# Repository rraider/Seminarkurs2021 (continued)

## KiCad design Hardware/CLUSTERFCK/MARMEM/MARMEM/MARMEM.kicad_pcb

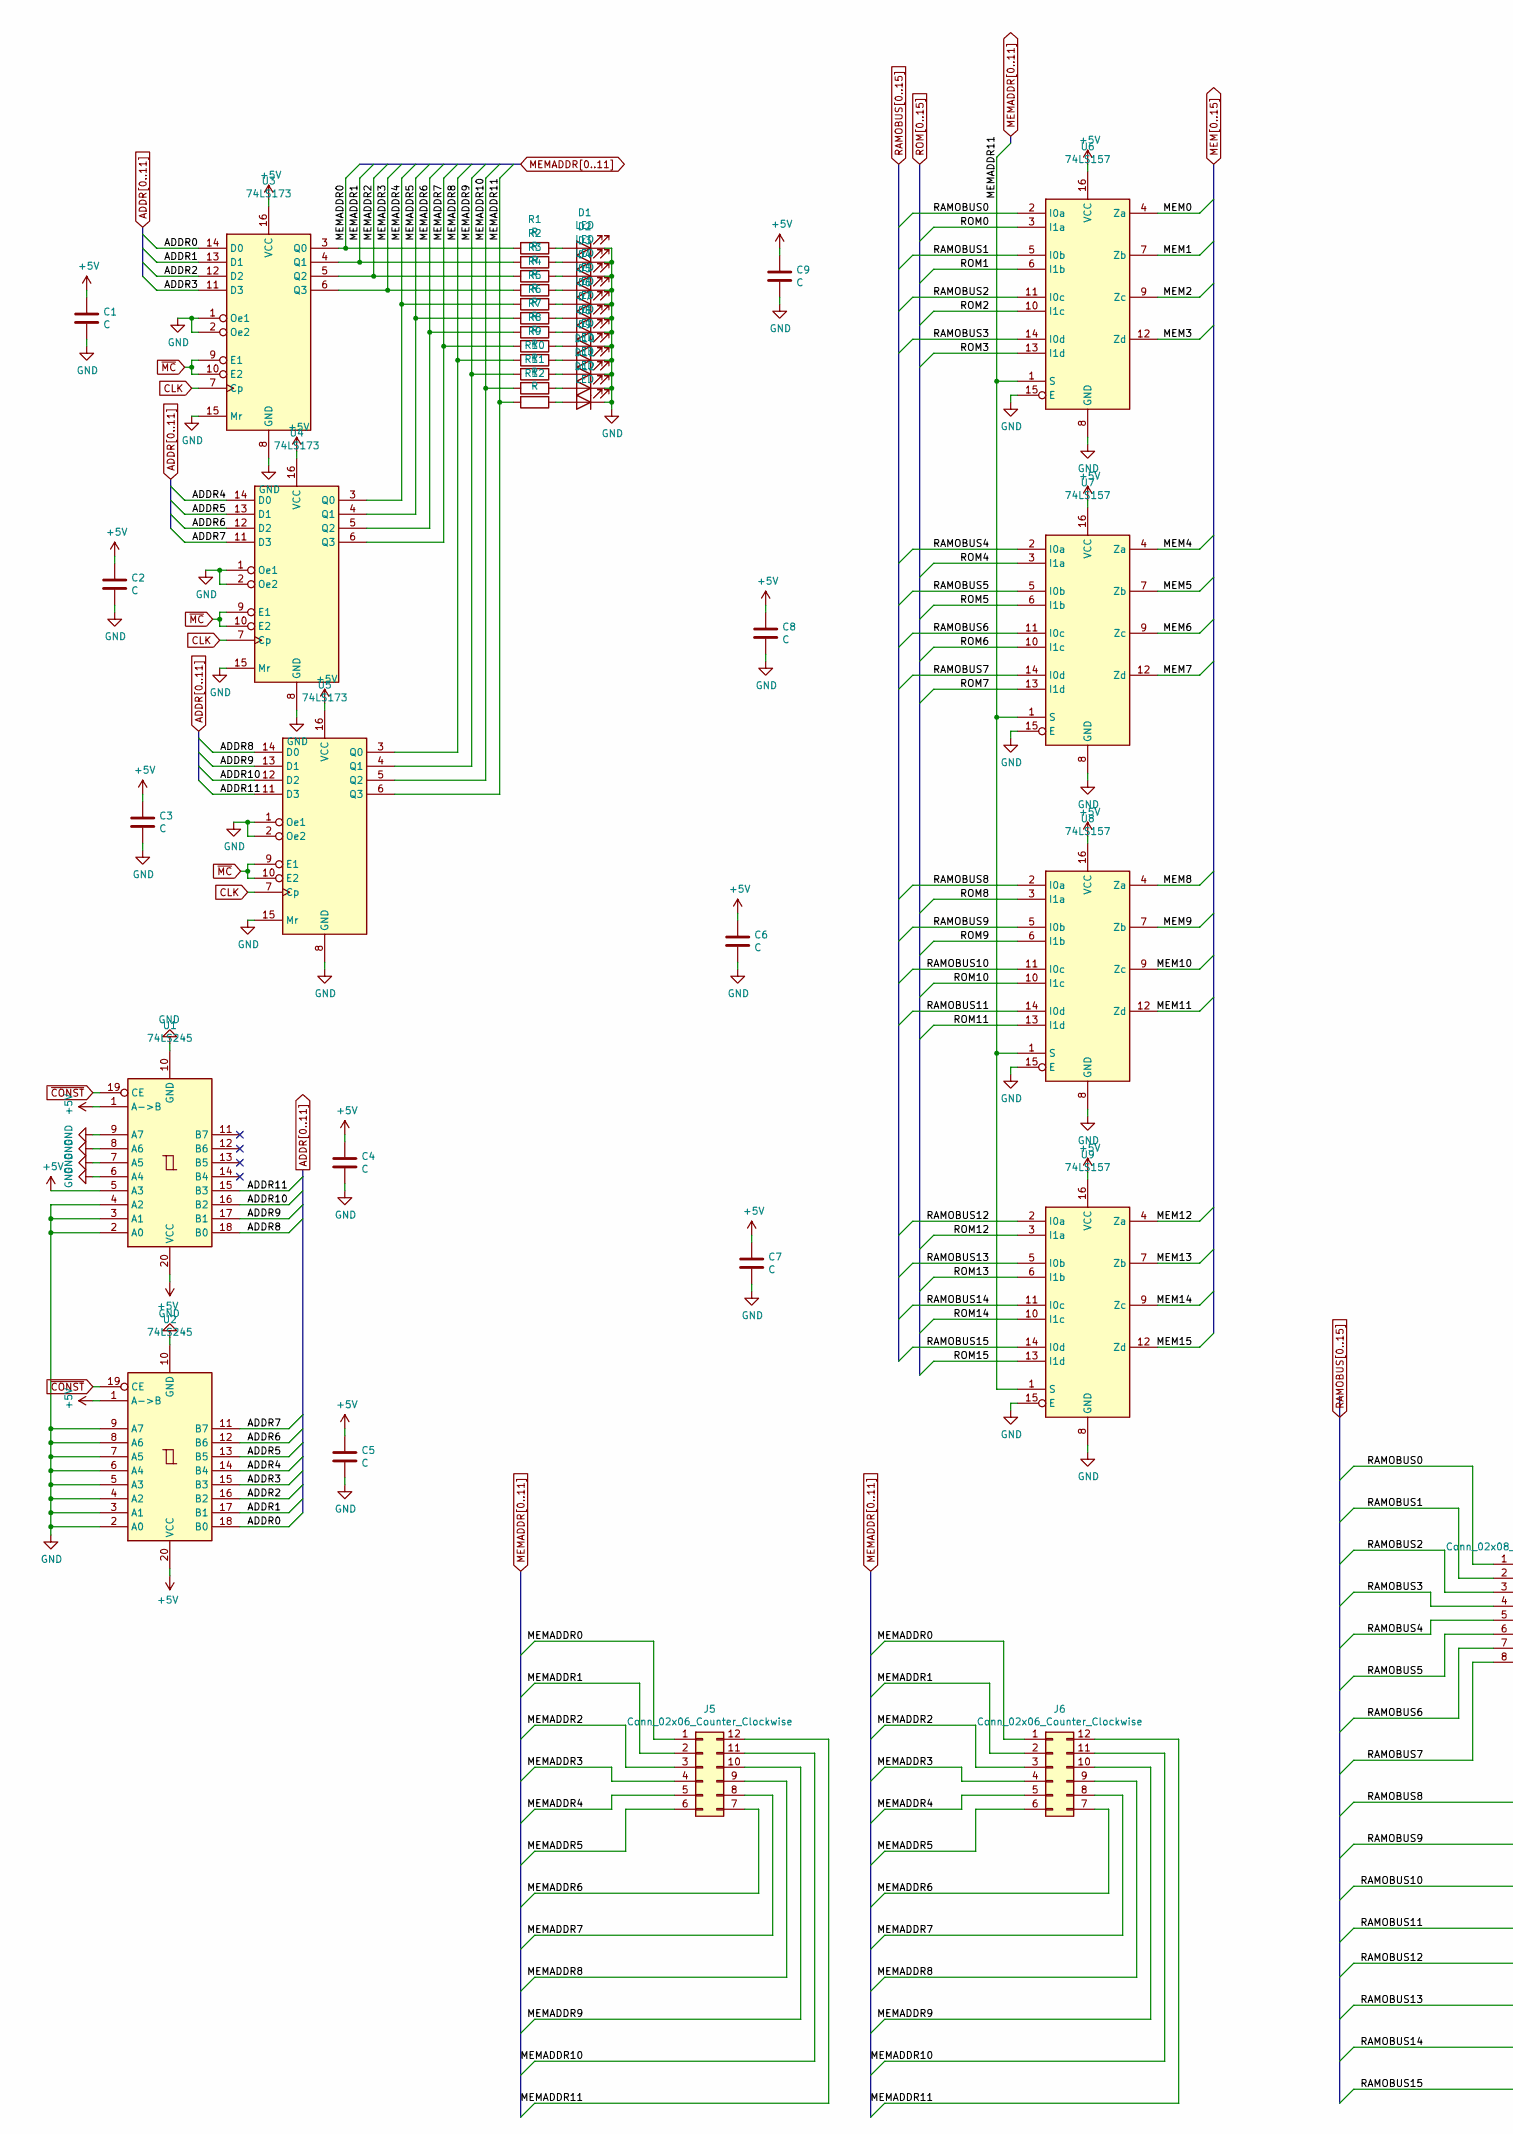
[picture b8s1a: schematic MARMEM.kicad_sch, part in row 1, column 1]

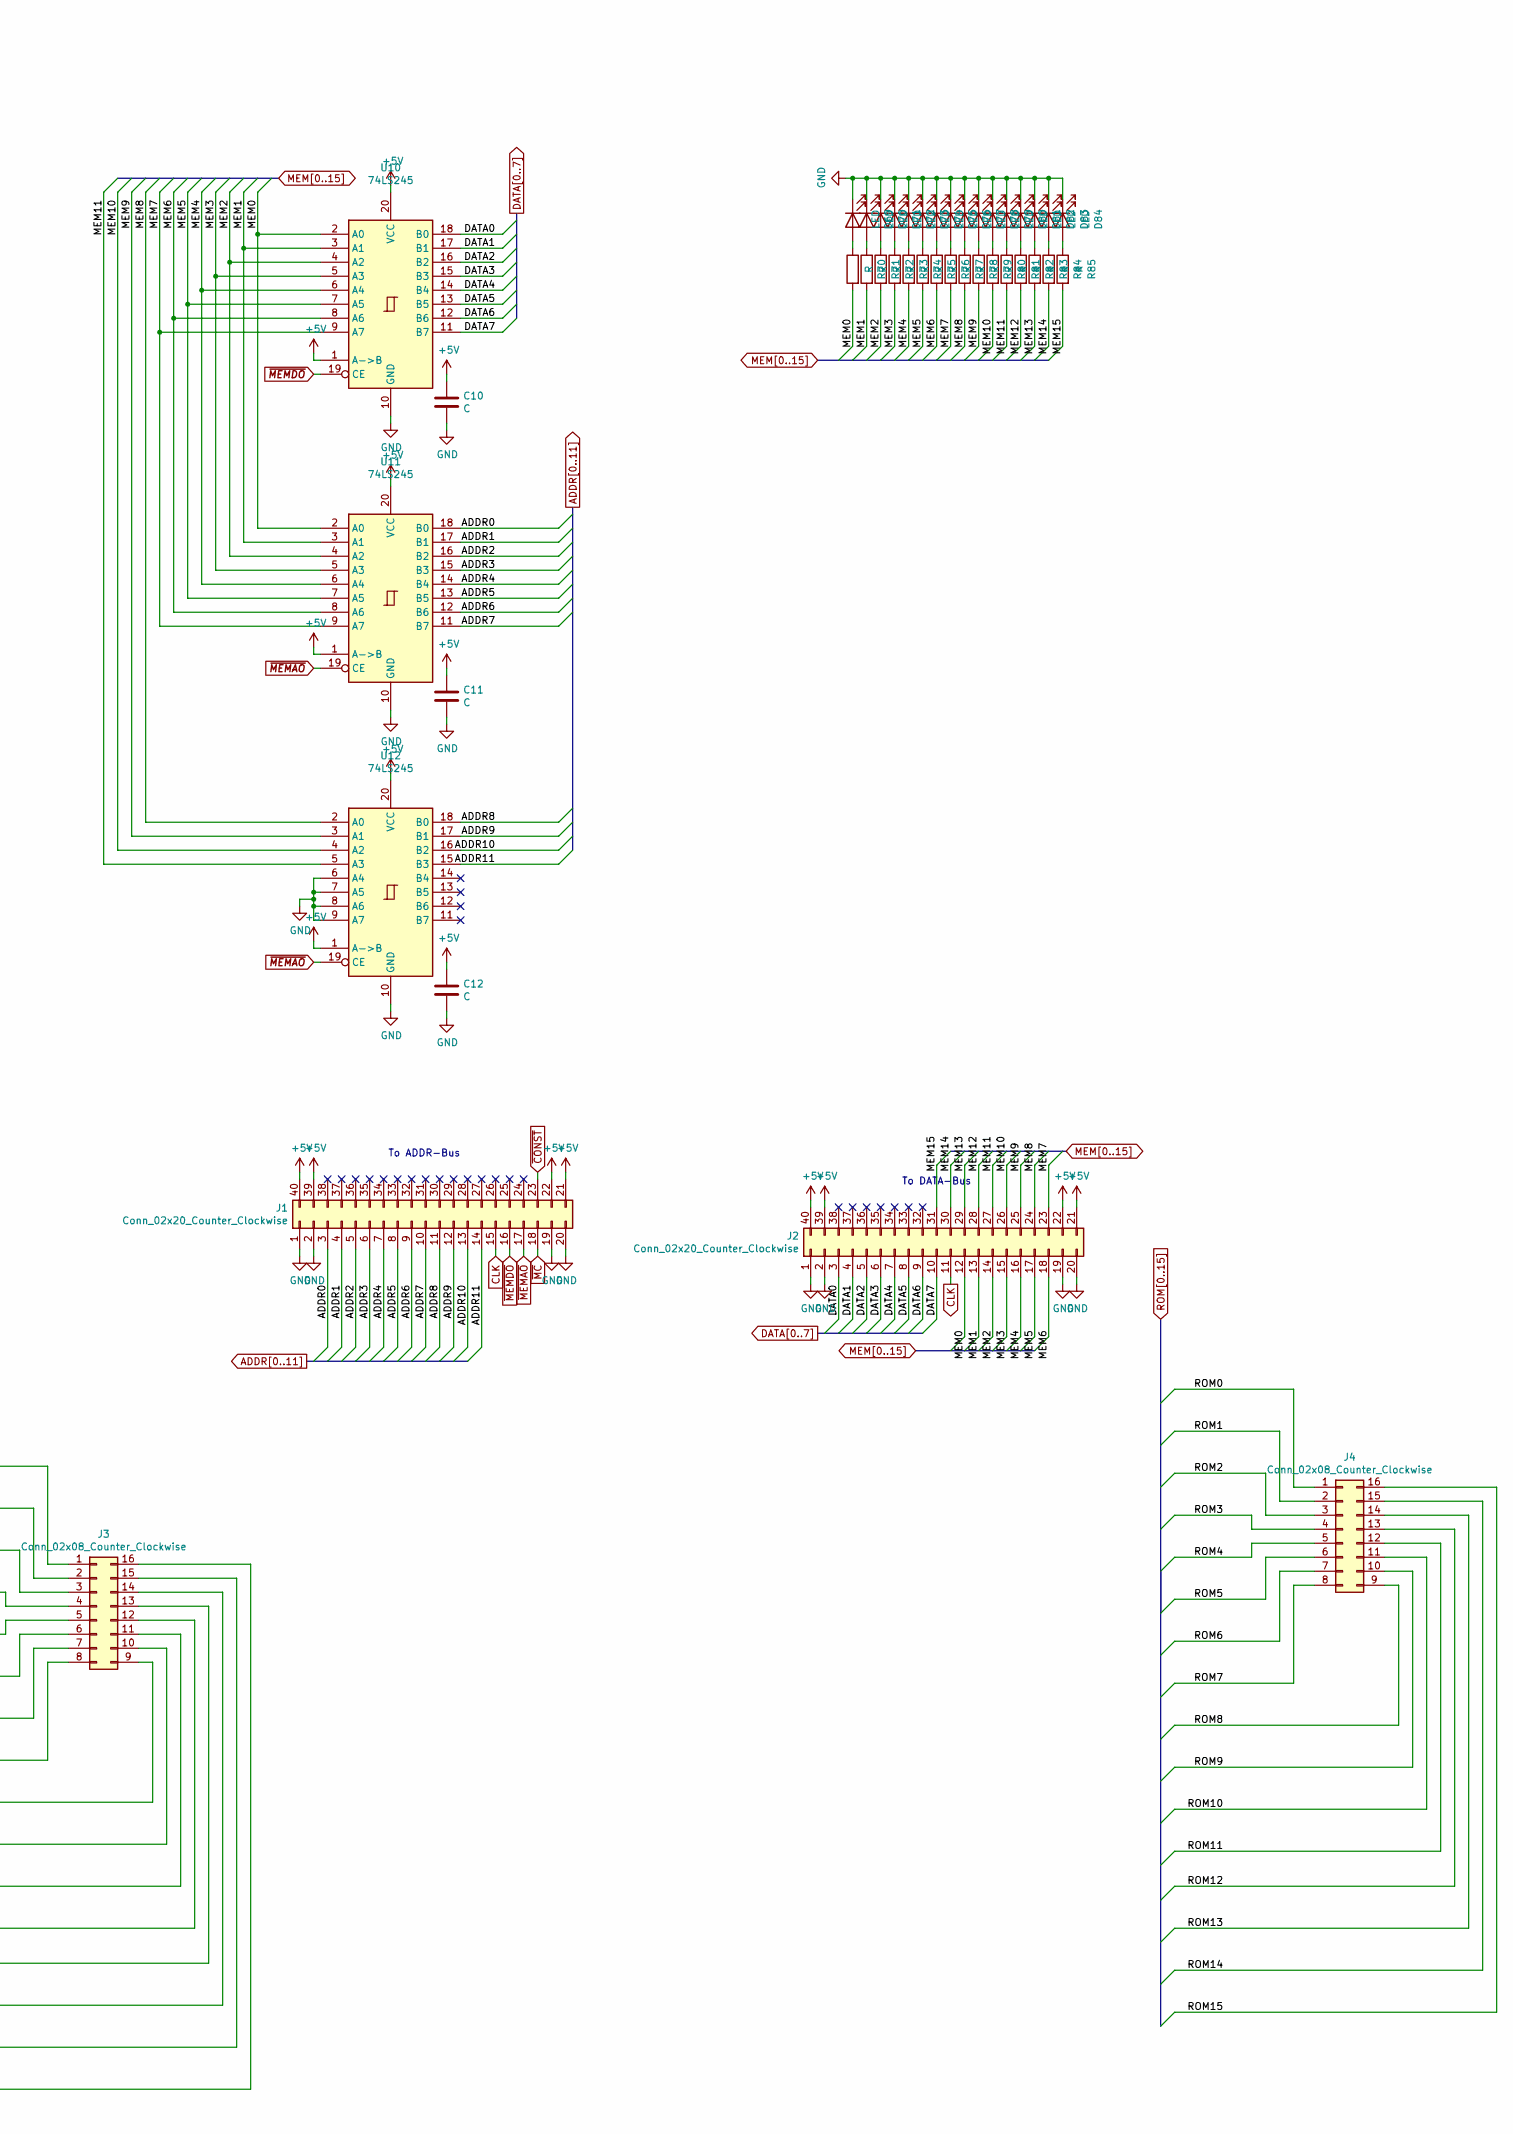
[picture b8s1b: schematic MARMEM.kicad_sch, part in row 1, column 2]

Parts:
C1, C2, C3, C4, C5, C6, C7, C8, C9, C10, C11, C12: C; C_0805_2012Metric_Pad1.15x1.40mm_HandSolder
D1, D2, D3, D4, D5, D6, D7, D8, D9, D10, D11, D12, D69, D70, D71, D72, D73, D74, D75, D76, D77, D78, D79, D80, D81, D82, D83, D84: LED; LED_D5.0mm
J1, J2: Conn_02x20_Counter_Clockwise; PinSocket_2x20_P2.54mm_Horizontal
J3, J4: Conn_02x08_Counter_Clockwise; PinHeader_2x08_P2.54mm_Horizontal
J5, J6: Conn_02x06_Counter_Clockwise; PinHeader_2x06_P2.54mm_Horizontal
R1, R2, R3, R4, R5, R6, R7, R8, R9, R10, R11, R12, R70, R71, R72, R73, R74, R75, R76, R77, R78, R79, R80, R81, R82, R83, R84, R85: R; R_0805_2012Metric_Pad1.15x1.40mm_HandSolder
U1, U2, U10, U11, U12: 74LS245; SOIC-20W_7.5x12.8mm_P1.27mm
U3, U4, U5: 74LS173; SOP-16_3.9x9.9mm_P1.27mm
U6, U7, U8, U9: 74LS157; SOP-16_3.9x9.9mm_P1.27mm

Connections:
+5V: C1.1, C2.1, C3.1, C4.1, C5.1, C6.1, C7.1, C8.1, C9.1, C10.1, C11.1, C12.1, J1.21, J1.22, J1.39, J1.40, J2.21, J2.22, J2.39, J2.40, U1.1 (A->B), U1.5 (A3), U1.20 (VCC), U2.1 (A->B), U2.20 (VCC), U3.16 (VCC), U4.16 (VCC), U5.16 (VCC), U6.16 (VCC), U7.16 (VCC), U8.16 (VCC), U9.16 (VCC), U10.1 (A->B), U10.20 (VCC), U11.1 (A->B), U11.20 (VCC), U12.1 (A->B), U12.20 (VCC)
ADDR0: J1.3, U2.18 (B0), U3.14 (D0), U11.18 (B0)
ADDR1: J1.4, U2.17 (B1), U3.13 (D1), U11.17 (B1)
ADDR2: J1.5, U2.16 (B2), U3.12 (D2), U11.16 (B2)
ADDR3: J1.6, U2.15 (B3), U3.11 (D3), U11.15 (B3)
ADDR4: J1.7, U2.14 (B4), U4.14 (D0), U11.14 (B4)
ADDR5: J1.8, U2.13 (B5), U4.13 (D1), U11.13 (B5)
ADDR6: J1.9, U2.12 (B6), U4.12 (D2), U11.12 (B6)
ADDR7: J1.10, U2.11 (B7), U4.11 (D3), U11.11 (B7)
ADDR8: J1.11, U1.18 (B0), U5.14 (D0), U12.18 (B0)
ADDR9: J1.12, U1.17 (B1), U5.13 (D1), U12.17 (B1)
ADDR10: J1.13, U1.16 (B2), U5.12 (D2), U12.16 (B2)
ADDR11: J1.14, U1.15 (B3), U5.11 (D3), U12.15 (B3)
CLK: J1.15, J2.11, U3.7 (Cp), U4.7 (Cp), U5.7 (Cp)
DATA0: J2.3, U10.18 (B0)
DATA1: J2.4, U10.17 (B1)
DATA2: J2.5, U10.16 (B2)
DATA3: J2.6, U10.15 (B3)
DATA4: J2.7, U10.14 (B4)
DATA5: J2.8, U10.13 (B5)
DATA6: J2.9, U10.12 (B6)
DATA7: J2.10, U10.11 (B7)
GND: C1.2, C2.2, C3.2, C4.2, C5.2, C6.2, C7.2, C8.2, C9.2, C10.2, C11.2, C12.2, D1.1 (K), D2.1 (K), D3.1 (K), D4.1 (K), D5.1 (K), D6.1 (K), D7.1 (K), D8.1 (K), D9.1 (K), D10.1 (K), D11.1 (K), D12.1 (K), D69.1 (K), D70.1 (K), D71.1 (K), D72.1 (K), D73.1 (K), D74.1 (K), D75.1 (K), D76.1 (K), D77.1 (K), D78.1 (K), D79.1 (K), D80.1 (K), D81.1 (K), D82.1 (K), D83.1 (K), D84.1 (K), J1.1, J1.2, J1.19, J1.20, J2.1, J2.2, J2.19, J2.20, U1.2 (A0), U1.3 (A1), U1.4 (A2), U1.6 (A4), U1.7 (A5), U1.8 (A6), U1.9 (A7), U1.10 (GND), U2.2 (A0), U2.3 (A1), U2.4 (A2), U2.5 (A3), U2.6 (A4), U2.7 (A5), U2.8 (A6), U2.9 (A7), U2.10 (GND), U3.1 (Oe1), U3.2 (Oe2), U3.8 (GND), U3.15 (Mr), U4.1 (Oe1), U4.2 (Oe2), U4.8 (GND), U4.15 (Mr), U5.1 (Oe1), U5.2 (Oe2), U5.8 (GND), U5.15 (Mr), U6.8 (GND), U6.15 (E), U7.8 (GND), U7.15 (E), U8.8 (GND), U8.15 (E), U9.8 (GND), U9.15 (E), U10.10 (GND), U11.10 (GND), U12.6 (A4), U12.7 (A5), U12.8 (A6), U12.9 (A7), U12.10 (GND)
MEM0: J2.12, R70.2, U6.4 (Za), U10.2 (A0), U11.2 (A0)
MEM1: J2.13, R71.2, U6.7 (Zb), U10.3 (A1), U11.3 (A1)
MEM2: J2.14, R72.2, U6.9 (Zc), U10.4 (A2), U11.4 (A2)
MEM3: J2.15, R73.2, U6.12 (Zd), U10.5 (A3), U11.5 (A3)
MEM4: J2.16, R74.2, U7.4 (Za), U10.6 (A4), U11.6 (A4)
MEM5: J2.17, R75.2, U7.7 (Zb), U10.7 (A5), U11.7 (A5)
MEM6: J2.18, R76.2, U7.9 (Zc), U10.8 (A6), U11.8 (A6)
MEM7: J2.23, R77.2, U7.12 (Zd), U10.9 (A7), U11.9 (A7)
MEM8: J2.24, R78.2, U8.4 (Za), U12.2 (A0)
MEM9: J2.25, R79.2, U8.7 (Zb), U12.3 (A1)
MEM10: J2.26, R80.2, U8.9 (Zc), U12.4 (A2)
MEM11: J2.27, R81.2, U8.12 (Zd), U12.5 (A3)
MEM12: J2.28, R82.2, U9.4 (Za)
MEM13: J2.29, R83.2, U9.7 (Zb)
MEM14: J2.30, R84.2, U9.9 (Zc)
MEM15: J2.31, R85.2, U9.12 (Zd)
MEMADDR0: J5.1, J6.1, R1.2, U3.3 (Q0)
MEMADDR1: J5.2, J6.2, R2.2, U3.4 (Q1)
MEMADDR2: J5.3, J6.3, R3.2, U3.5 (Q2)
MEMADDR3: J5.4, J6.4, R4.2, U3.6 (Q3)
MEMADDR4: J5.5, J6.5, R5.2, U4.3 (Q0)
MEMADDR5: J5.6, J6.6, R6.2, U4.4 (Q1)
MEMADDR6: J5.7, J6.7, R7.2, U4.5 (Q2)
MEMADDR7: J5.8, J6.8, R8.2, U4.6 (Q3)
MEMADDR8: J5.9, J6.9, R9.2, U5.3 (Q0)
MEMADDR9: J5.10, J6.10, R10.2, U5.4 (Q1)
MEMADDR10: J5.11, J6.11, R11.2, U5.5 (Q2)
MEMADDR11: J5.12, J6.12, R12.2, U5.6 (Q3), U6.1 (S), U7.1 (S), U8.1 (S), U9.1 (S)
unnamed: D1.2 (A), R1.1
unnamed: D2.2 (A), R2.1
unnamed: D3.2 (A), R3.1
unnamed: D4.2 (A), R4.1
unnamed: D5.2 (A), R5.1
unnamed: D6.2 (A), R6.1
unnamed: D7.2 (A), R7.1
unnamed: D8.2 (A), R8.1
unnamed: D9.2 (A), R9.1
unnamed: D10.2 (A), R10.1
unnamed: D11.2 (A), R11.1
unnamed: D12.2 (A), R12.1
unnamed: D69.2 (A), R70.1
unnamed: D70.2 (A), R71.1
unnamed: D71.2 (A), R72.1
unnamed: D72.2 (A), R73.1
unnamed: D73.2 (A), R74.1
unnamed: D74.2 (A), R75.1
unnamed: D75.2 (A), R76.1
unnamed: D76.2 (A), R77.1
unnamed: D77.2 (A), R78.1
unnamed: D78.2 (A), R79.1
unnamed: D79.2 (A), R80.1
unnamed: D80.2 (A), R81.1
unnamed: D81.2 (A), R82.1
unnamed: D82.2 (A), R83.1
unnamed: D83.2 (A), R84.1
unnamed: D84.2 (A), R85.1
RAMOBUS0: J3.1, U6.2 (I0a)
RAMOBUS1: J3.2, U6.5 (I0b)
RAMOBUS2: J3.3, U6.11 (I0c)
RAMOBUS3: J3.4, U6.14 (I0d)
RAMOBUS4: J3.5, U7.2 (I0a)
RAMOBUS5: J3.6, U7.5 (I0b)
RAMOBUS6: J3.7, U7.11 (I0c)
RAMOBUS7: J3.8, U7.14 (I0d)
RAMOBUS8: J3.9, U8.2 (I0a)
RAMOBUS9: J3.10, U8.5 (I0b)
RAMOBUS10: J3.11, U8.11 (I0c)
RAMOBUS11: J3.12, U8.14 (I0d)
RAMOBUS12: J3.13, U9.2 (I0a)
RAMOBUS13: J3.14, U9.5 (I0b)
RAMOBUS14: J3.15, U9.11 (I0c)
RAMOBUS15: J3.16, U9.14 (I0d)
ROM0: J4.1, U6.3 (I1a)
ROM1: J4.2, U6.6 (I1b)
ROM2: J4.3, U6.10 (I1c)
ROM3: J4.4, U6.13 (I1d)
ROM4: J4.5, U7.3 (I1a)
ROM5: J4.6, U7.6 (I1b)
ROM6: J4.7, U7.10 (I1c)
ROM7: J4.8, U7.13 (I1d)
ROM8: J4.9, U8.3 (I1a)
ROM9: J4.10, U8.6 (I1b)
ROM10: J4.11, U8.10 (I1c)
ROM11: J4.12, U8.13 (I1d)
ROM12: J4.13, U9.3 (I1a)
ROM13: J4.14, U9.6 (I1b)
ROM14: J4.15, U9.10 (I1c)
ROM15: J4.16, U9.13 (I1d)
~CONST: J1.23, U1.19 (CE), U2.19 (CE)
~MC: J1.18, U3.9 (E1), U3.10 (E2), U4.9 (E1), U4.10 (E2), U5.9 (E1), U5.10 (E2)
~MEMAO: J1.17, U11.19 (CE), U12.19 (CE)
~MEMDO: J1.16, U10.19 (CE)

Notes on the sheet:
To ADDR-Bus
To DATA-Bus

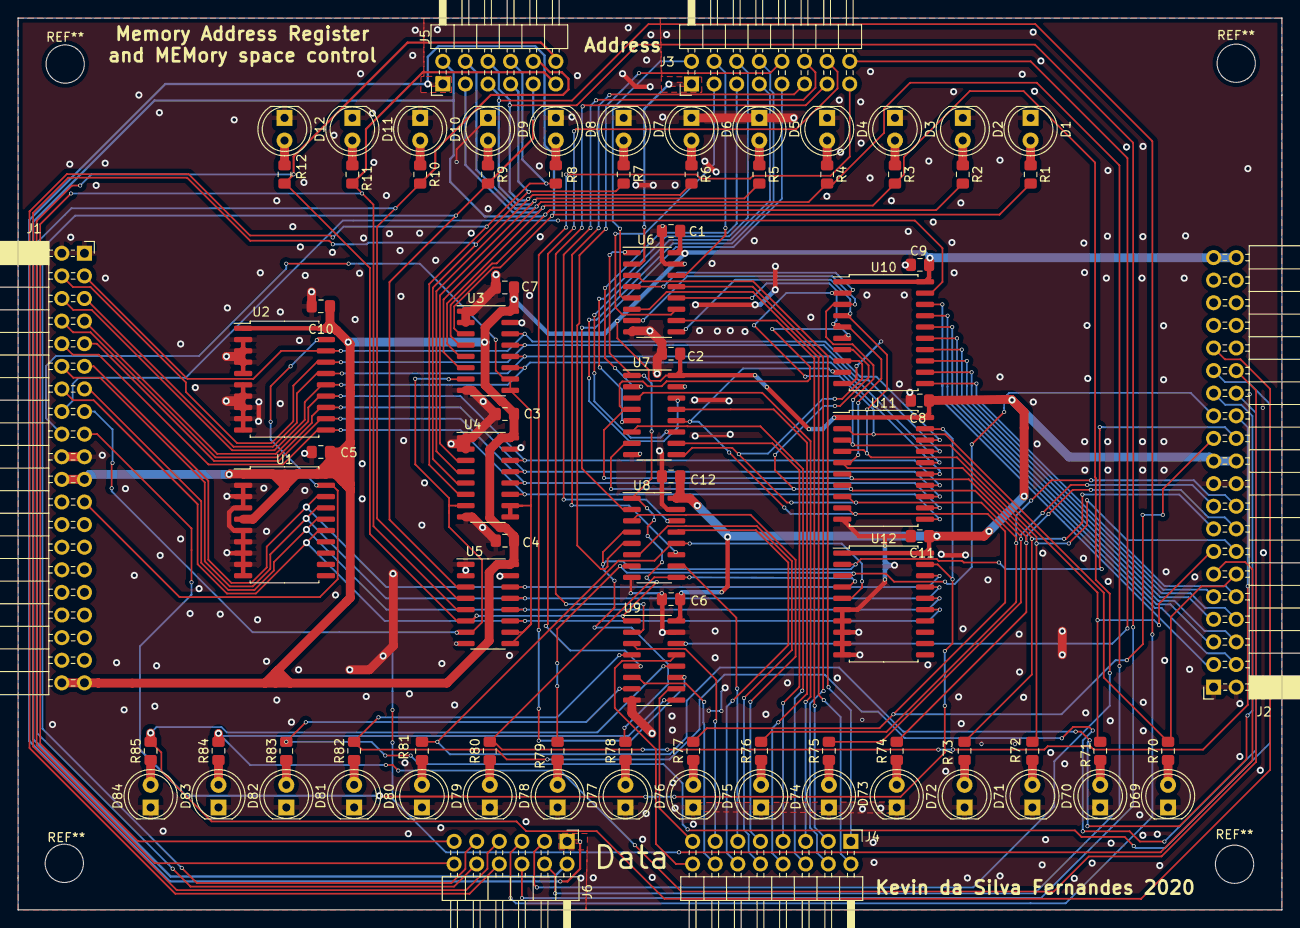
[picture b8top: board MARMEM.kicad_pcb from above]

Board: 2 copper layers, 142.0 x 100.2 mm, 86 parts (0 on the bottom side), 115 nets.

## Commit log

2020-05-05 added lib folder
2020-05-06 finished ALU
2020-05-06 added main file
2020-05-06 added regsiter A and B
2020-05-06 wir essen jetzt
2020-05-06 added bugfixes @ALU and REG-A/B. Also added tunneling system @main
2020-05-06 created REG_INST
2020-05-06 added opcodes.txt & minor improvements
2020-05-06 added basic opcodes
2020-05-06 added clock mechanism
2020-05-06 foobar
2020-05-06 added PC
2020-05-06 added ROM wiring
2020-05-06 added ram
2020-05-06 created uINST
2020-05-06 added flags.txt
2020-05-06 added EQL funcion to ALU
2020-05-06 splitted flags
2020-05-06 ich geh jetzt pennen, gute Nacht :3
2020-05-06 enlarged uINST
2020-05-07 modified uINST
2020-05-07 created DECODER
2020-05-07 created GFX
2020-05-07 added mission patch template
2020-05-07 wired up main
2020-05-07 added GFX to main
2020-05-07 modified main
2020-05-07 added FET to opcodes
2020-05-07 created dir opcodesDefinition; created FET
2020-05-07 created NOP
2020-05-07 created ADD; modified NOP
2020-05-07 created SUB
2020-05-07 modified NOP; modified FET; created LDAa
2020-05-07 created LDAc
2020-05-07 created LDBa
2020-05-07 created LDBc
2020-05-07 created MAR
2020-05-07 created MAR; modified main
2020-05-07 changed flags in main and uINST
2020-05-07 added architecture diagram and beginning of mission patch
2020-05-07 major bugfixes in ALU and PC
2020-05-07 added missionpatch rev2
2020-05-07 added LED matrix to main file
2020-05-07 created JMP
2020-05-07 modified FET
2020-05-07 modified ADD
2020-05-07 modified LDAa
2020-05-07 modified LDBa
2020-05-07 modified SUB
2020-05-07 created JMPZ
2020-05-07 created JMPC
2020-05-07 debugged main
2020-05-07 modified uINST; modified main; created GFX
2020-05-07 created HALT
2020-05-07 updated opcodes
2020-05-07 moved opcodes.txt to opcodesDefinition/_opcodes.txt
2020-05-07 modified uINST eprom C
2020-05-07 modified uINST eprom B
2020-05-07 modified opcodesDefinition/_opcodes
2020-05-07 modified uINST eprom A
2020-05-07 added fibonacci code
2020-05-07 debugged uINST
2020-05-07 major fixes
2020-05-07 programmed ROM with fibonacci code
2020-05-07 added debug electronics && auf Kev warten
2020-05-07 fix in uINST
2020-05-07 added debug 4 ALU and REG A/B
2020-05-07 modified uINST eproms
2020-05-07 fixed code
2020-05-07 FINALIZED V1.0 - STABLE PUSH
2020-05-08 downgraded PC from 12 bit to 11 bit
2020-05-08 random
2020-05-08 modified main flags; modified uINST outputs
2020-05-08 added hw subroutine functionality
2020-05-10 created Assembly-to-Machine-Compiler, see assembler/Syntax for info on usage
2020-05-10 added GFX txt
2020-05-10 added GFX ADDR table
2020-05-10 added helloWorld program
2020-05-10 added architecture2 and updated missionpatch
2020-05-10 fixed helloWorld.txt
2020-05-10 fixed HelloWorld.txt again :D
2020-05-10 fixed gfx.txt
2020-05-10 fixed gfx.txt again
2020-05-10 fixed gfx AGAIN :/
2020-05-10 added gfx support in compiler
2020-05-10 fixed screen res
2020-05-10 created and implemented opcode EXT
2020-05-10 STABLE PUSH V2
2020-05-10 modified assembler/Syntax
2020-05-16 added partlist
2020-05-16 started hardware
2020-05-17 finished ALU arithmetic
2020-05-17 finished zero and equal flags
2020-05-17 ich geh jz pennen gn :)
2020-05-25 random push
2020-05-26 im tired
2020-05-26 *yawns*
2020-05-26 started making uINST
2020-05-26 finished uINST in schematic
2020-05-28 finished schematic
2020-05-29 mach du mal
2020-05-29 enlarged ram to 2k16 and added support for running code from ram
2020-05-30 upgraded rom to 8k8, ability to hold 4 programs at once
2020-05-30 updated compiler; minor efficiency improvements in schematic
2020-05-31 added forced jmp-instruction at end of program memory in rom
2020-05-31 Create LICENSE
2020-05-31 assigned footprints
2020-06-01 done stuff
2020-06-01 existance is pain
2020-06-22 tmp push
2020-06-22 started with reg a & b
2020-06-23 added subtraction to Reg B
2020-06-23 schule aus
2020-07-08 updated subroutine opcodes for stack implementation
2020-07-08 updated compiler with implemented stack
2020-07-17 began clusterfuck
2020-07-17 updated Syntax
2020-07-19 wrote test program for stack
2020-09-17 new version 2.1
2020-09-17 minor changes
2020-09-19 15:00 - 19:00; 21:30 - 22:30 updated spu2.1 added opcode SOT implemented opcode SOT in Digital added table indicator recoded flag eeproms
2020-09-20 14:00 - 15:50 updated compiler to include opcode SOT fixed incorrect code in compiler compiled HelloStack ASM file for use in Digital fixed incorrect values in flag eeproms encountered problem with s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
    thoughts:
    data with 0x08XX const for stack
    data and addr parallel in ram because never active simultaneously
    => does not workbecause of const for stack
    => new flag RAMI -> RAMDI,RAMAI
2020-09-20 17:20 - 18:30 split flag RAMI up into RAMDI and RAMAI updated flag use in the following opcodes: - ADD - SUB - JSUB - RSUB fixed incorrect values in flag eeproms HelloStack runs without complications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
2020-09-21 #0001 | 5min | created template for commit messages
2020-09-21 C:/Program Files/Git/usr/bin/bash002 | 1h | review and minor changes#
2020-09-21 0003 | 0h | fixed incorrect values in flag eproms
2020-10-03 0005 | 0h | Digital changes
2020-10-03 0004 | 2h | added CLUSTERFCK/CLK scematic
2020-10-03 created CLUSTERFUCK/MAR
2020-10-03 0007 | 1,5 | created CLUSTERFCK/PC
2020-10-03 0010 | 3h | created CLUSTERFCK/RAM
2020-10-06 0011 | 1,5 | modified CLUSTERFCK/RAM
2020-10-06 12 | 5h | CLUSTERFUCK/ALU
2020-10-06 13 | 1h | CLUSTERFCK/REG_A+REG_B
2020-10-06 14 | 1h | CLUSTERFUCK/ROM
2020-10-09 8 | 12h | GFX Modul + Einarbeitung
2020-10-09 0015 | 0h | changed metadata in CLUSTERFCK/PC
2020-10-10 16 | 1h | Added powerSupply to CLK module
2020-10-10 17 | 1h | beautifyed several scematics
2020-10-10 18 | 5min | Added excess NANDs to RAM module
2020-10-10 0019 | 1,5h | created CLUSTERFCK/MIM
2020-10-10 0020 | 0,5 | created CLUSTERFCK/IR
2020-10-12 0021 | 0,1h | created CLUSTERFCK/ADDR
2020-10-12 0022 | 0,1h | created CLUSTERFCK/DATA
2020-10-12 0023 | 0,2h | created CLUSTERFCK/PO; meta
2020-10-12 0024 | 0,2h | created CLUSTERFCK/CONST
2020-10-12 0025 | 0,3h | mirrored stackpointer to LED-array
2020-10-14 0027 | 0,2h | updated CLUSTERFCK/MAR
2020-10-15 Add files via upload
    Die Restlichen Zeichnungen
2020-10-25 29 | 22h | Layoutet GFX Module
2020-11-04 0030 | 4,5h | Review GFX
2020-11-11 0031 | 10h | PCB MARMEM
2020-11-16 unstable switching device push
2020-11-16 0032| 1 | Final cosmetics on GFX
2020-11-16 0034 | 1h | review of MARMEM Module
2020-11-20 minor fixes
2020-11-21 0035 | 1,5h | Correction MARMEM
2020-11-21 0036 | 5,2h | Layout MIM
2020-11-22 0037 | 0,5h | git training
2020-11-23 0033 | 10h | PCB design test CLK Module
2020-11-26 0038 | 0,5h | review marmem
2020-11-26 quick fix MARMEM
2020-11-26 0039 | 0,5h | review MIM
2020-11-27 0040 | 6 | STDLN CLK REV 2
2020-11-27 0041 | 0,1h | review STDLN CLK REV 2
2020-11-27 quickfix CLK_STDLN
2020-11-30 0042 | 6h | Layout PC
2020-12-01 quickfix PC silkscreen
2020-12-02 quickfix pc
2020-12-03 temporary unstable push
2020-12-10 0043 | 3h | Layout IR
2020-12-11 quickfix IR groundplane connections
2020-12-14 0044 | 0,2 | Review IR by Leon
2020-12-23 0046|6|Alu Module
2020-12-23 0047 | 0.5h | review ALU Module
2020-12-24 0048 | 5h | Layout ROM
2020-12-26 0049 | 1h | review ROM
2020-12-26 0049 | 1h | review ROM 2
2020-12-28 marmem wieder in git
2020-12-28 0052 | 4h | MARMEM update
2020-12-28 0053 | 3h | Layout REG_A
2020-12-28 0054 | 0,5h | review REG_A
2020-12-28 git add .git add .git add . BACKUP git add .git add .git add .
2020-12-29 0050 | 5h | Ram module
2020-12-30 0055 | 2h | Review RAM
2021-01-04 0056|2|PO Module
2021-01-04 0045 | 6h | CLK module rev 3
2021-01-06 0059 | 1h | Design & Layout JUMPER
2021-01-06 0059 | 0,5h | Review JUMPER
2021-01-06 0060 | 2h | 2nd review GFX
2021-01-06 updated architecture
2021-01-06 0061|1h|PO Module Versuch 2
2021-01-06 0062 | 0 | review PO 2
2021-01-07 0063 | 0,1h | PO review 2.1
2021-01-08 0064 | 1h | logo design
2021-01-09 0065 | 24h | ADDR & DATA & PLACEHOLDER etc
2021-01-09 quickfix PO width
2021-01-09 0066 | 6h | made holes in pcbs
2021-01-09 UNSTABLE PUSH! RAM NOT WIRED!
2021-01-10 added renderings
2021-01-10 added step files
2021-01-10 added diagram
2021-01-11 0070 | 6h | completely rerouted RAM
2021-01-11 0071 | 0h | review RAM
2021-01-16 added silkscreen PNGs
2021-01-16 added JLC logo to JMPER
2021-01-17 0072 | 3h | make silkscreen prettier
2021-01-22 0073 | 2h | made parser for MIM eproms
2021-01-29 0074 | 0,2h | bugfix in MIMparser; created MIM binaries
2021-01-30 0075 | 0,3h | updated assembler
2021-01-31 0076 | 0,3h | bugfix in MIMparser; created MIM binaries
2021-01-31 quickfix bugfix MIMparser(return bit)
2021-02-22 0077 | 4h | various changes in high-level software
2021-03-09 added interview mp3
